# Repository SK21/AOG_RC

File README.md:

RateController (RC) is an add-on app that works with AgOpenGPS (https://github.com/agopengps-official/AgOpenGPS/) for product application rate control.

**RC Installation**
1.	Go to the latest release.
2.	Download RateControllerApp.zip
3.	Extract the file to a folder of your choice.
4.	Find and run RateController.exe

RC starts with the main screen. If AOG is connected the AOG icon will be green. There are icons for 5 products and fans. The icons will be green if connected. A module will show blue if it is sending data but not receiving. Red if there is a rate error and clear if not connected. Press the icons to show status information about the product. A graph shows the quantity remaining in the tank. Press 'Target Rate' to switch rate settings. Press Rx to use variable rate. Press 'Quantity' to switch settings. Press 'Area' to switch settings. Press quantity amount to reset tank. Press area amount to reset area.

  If there is a rate alarm due to over or under rate application a warning button will flash. The icon of the product in error will also flash. Press the warning button to silence the alarm.

  Most pages in the app menu have help available by pressing the '?'. Troubleshooting information can be found on the menu help page by pressing the '?'.

## Rate control repositories

- AOG_RC (main application)
  https://github.com/SK21/AOG_RC

- Rate_Control (module pcbs)
  https://github.com/AgOpenGPS-Official/Rate_Control

- PCBsetup (module firmware installation)
  https://github.com/SK21/PCBsetup

**Disclaimer**

This software is for discussion and learning. It is not in any way to be used on any physical equipment and is meant for use by a simulator only.

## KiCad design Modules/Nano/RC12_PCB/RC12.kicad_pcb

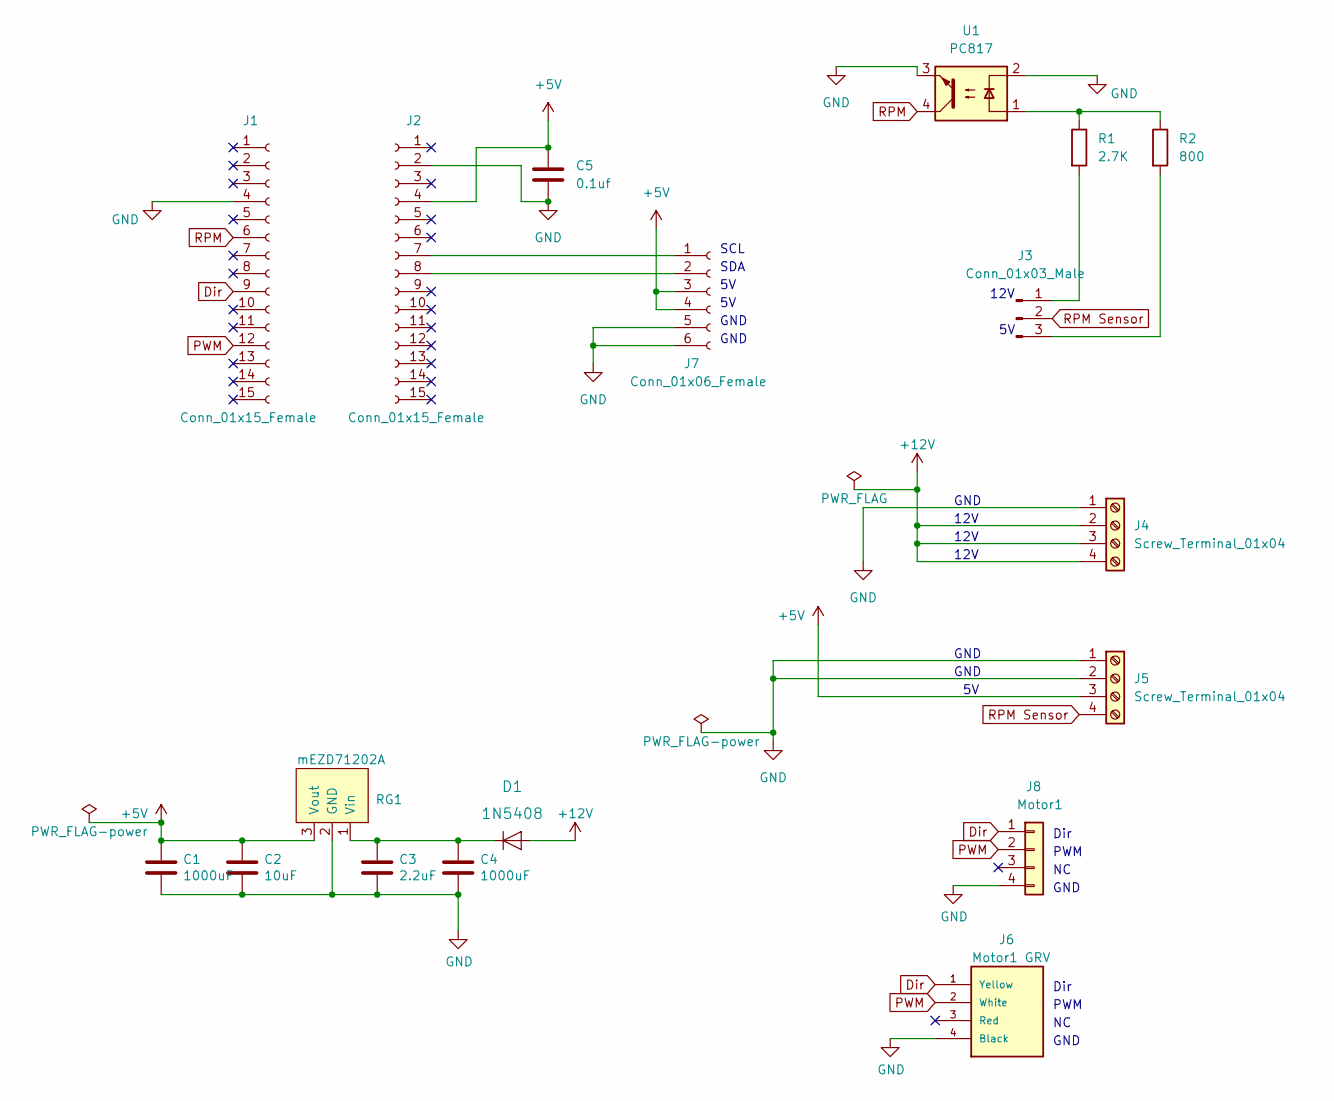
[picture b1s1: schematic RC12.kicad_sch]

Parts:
C1, C4: 1000uF; CP_Radial_D10.0mm_P5.00mm
C2: 10uF; C_Disc_D5.0mm_W2.5mm_P2.50mm
C3: 2.2uF; C_Disc_D5.0mm_W2.5mm_P2.50mm
C5: 0.1uf; C_Disc_D5.0mm_W2.5mm_P2.50mm
D1: 1N5408
J1, J2: Conn_01x15_Female; PinSocket_1x15_P2.54mm_Vertical
J3: Conn_01x03_Male; PinHeader_1x03_P2.54mm_Vertical
J4, J5: Screw_Terminal_01x04; TerminalBlock_Phoenix_PT-1,5-4-5.0-H_1x04_P5.00mm_Horizontal
J6: Motor1 GRV; Grove
J7: Conn_01x06_Female; PinSocket_1x06_P2.54mm_Vertical
J8: Motor1; Molex_KK-254_AE-6410-04A_1x04_P2.54mm_Vertical
R1: 2.7K; R_Axial_DIN0207_L6.3mm_D2.5mm_P10.16mm_Horizontal
R2: 800; R_Axial_DIN0207_L6.3mm_D2.5mm_P10.16mm_Horizontal
RG1: mEZD71202A; mEZD71201A
U1: PC817

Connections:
+5V: C1.1, C2.1, C5.2, J2.4, J5.3, J7.3, J7.4, RG1.3 (Vout)
+12V: D1.2 (A), J4.2, J4.3, J4.4
Dir: J1.9, J6.1 (Yellow), J8.1
GND: C1.2, C2.2, C3.2, C4.2, C5.1, J1.4, J2.2, J4.1, J5.1, J5.2, J6.4 (Black), J7.5, J7.6, J8.4, RG1.2 (GND), U1.2, U1.3
unnamed: C3.1, C4.1, D1.1 (C), RG1.1 (Vin)
unnamed: J2.7, J7.1
unnamed: J2.8, J7.2
unnamed: J3.1, R1.2
unnamed: J3.3, R2.2
unnamed: R1.1, R2.1, U1.1
PWM: J1.12, J6.2 (White), J8.2
RPM: J1.6, U1.4
RPM Sensor: J3.2, J5.4

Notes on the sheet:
SCL
SDA
Dir
12V
PWM
GND

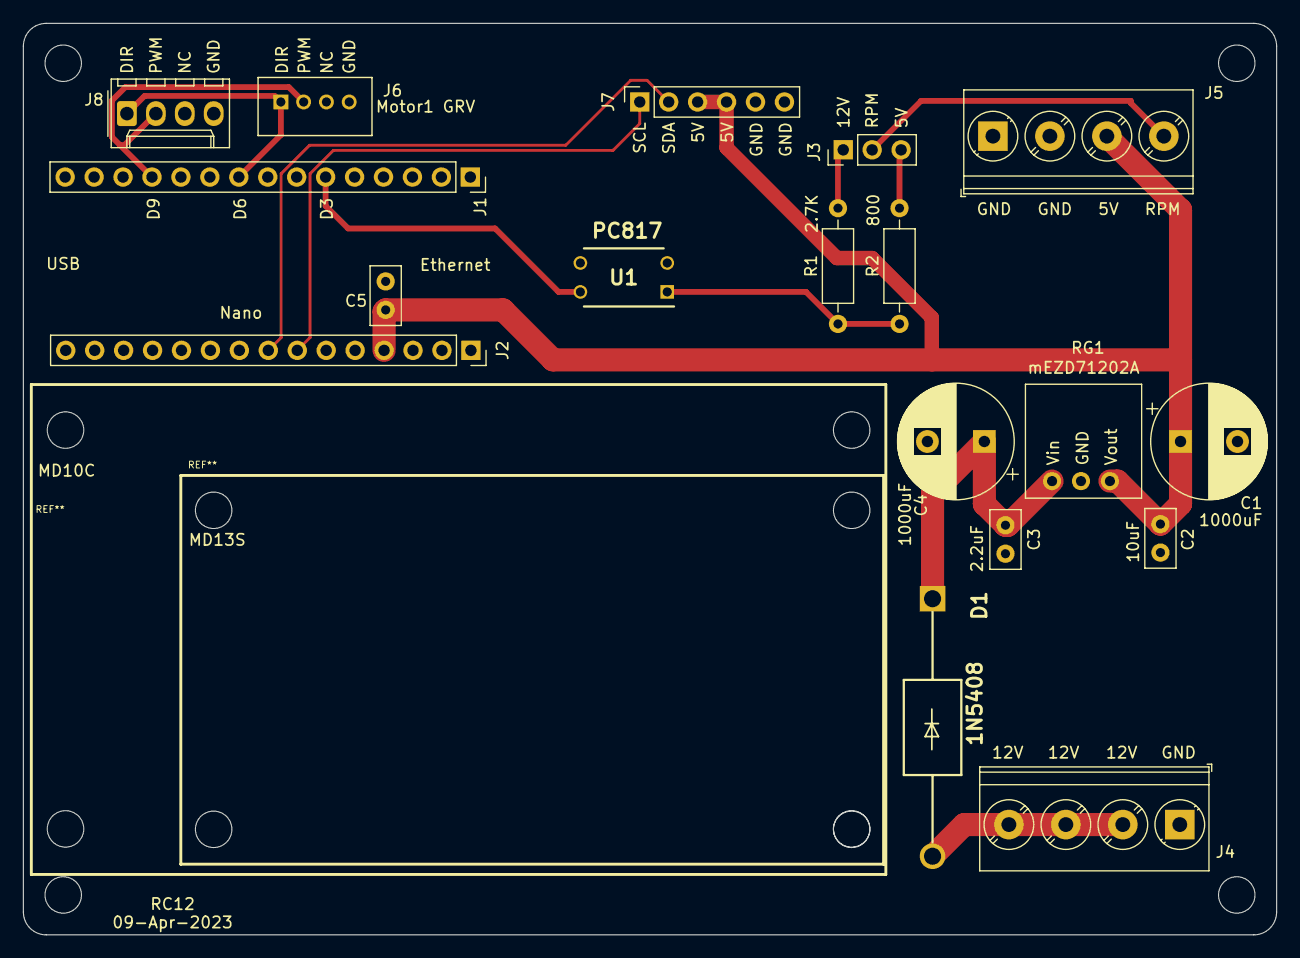
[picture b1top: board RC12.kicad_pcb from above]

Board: 2 copper layers, 110.0 x 80.0 mm, 22 parts (0 on the bottom side), 13 nets.

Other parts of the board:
 : MountingHole_3.2mm_M3
 #2,  #3,  #4: MountingHole_3.2mm_M3

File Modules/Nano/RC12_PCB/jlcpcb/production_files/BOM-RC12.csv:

Comment,Designator,Footprint,LCSC
PC817,U1,PC817,https://www.lcsc.com/product-detail/_Sharp-Microelectronics-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
,,PC817 socket,https://www.lcsc.com/product-detail/_Nextron-Nextronics-Engi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
Conn_01x15_Female,J2,PinSocket_1x15_P2.54mm_Vertical,
2.2uF,C3,C_Disc_D5.0mm_W2.5mm_P2.50mm,
Conn_01x15_Female,J1,PinSocket_1x15_P2.54mm_Vertical,
1000uF,C4,CP_Radial_D10.0mm_P5.00mm,
Screw_Terminal_01x04,J5,"TerminalBlock_Phoenix_PT-1,5-4-5.0-H_1x04_P5.00mm_Horizontal",
1000uF,C1,CP_Radial_D10.0mm_P5.00mm,
10uF,C2,C_Disc_D5.0mm_W2.5mm_P2.50mm,
Motor1 GRV,J6,Grove,https://jlcpcb.com/partdetail/SeeedStudio-110990030/C403774
0.1uf,C5,C_Disc_D5.0mm_W2.5mm_P2.50mm,
Screw_Terminal_01x04,J4,"TerminalBlock_Phoenix_PT-1,5-4-5.0-H_1x04_P5.00mm_Horizontal",
2.7K,R1,R_Axial_DIN0207_L6.3mm_D2.5mm_P10.16mm_Horizontal,
Conn_01x03_Male,J3,PinHeader_1x03_P2.54mm_Vertical,
800,R2,R_Axial_DIN0207_L6.3mm_D2.5mm_P10.16mm_Horizontal,
1N5408,D1,1N5408,
mEZD71202A,RG1,mEZD71201A,
Motor1,J8,Molex_KK-254_AE-6410-04A_1x04_P2.54mm_Vertical,https://www.lcsc.com/product-detail/_TE-Connectivity-_C86504.html
Conn_01x06_Female,J7,PinSocket_1x06_P2.54mm_Vertical,

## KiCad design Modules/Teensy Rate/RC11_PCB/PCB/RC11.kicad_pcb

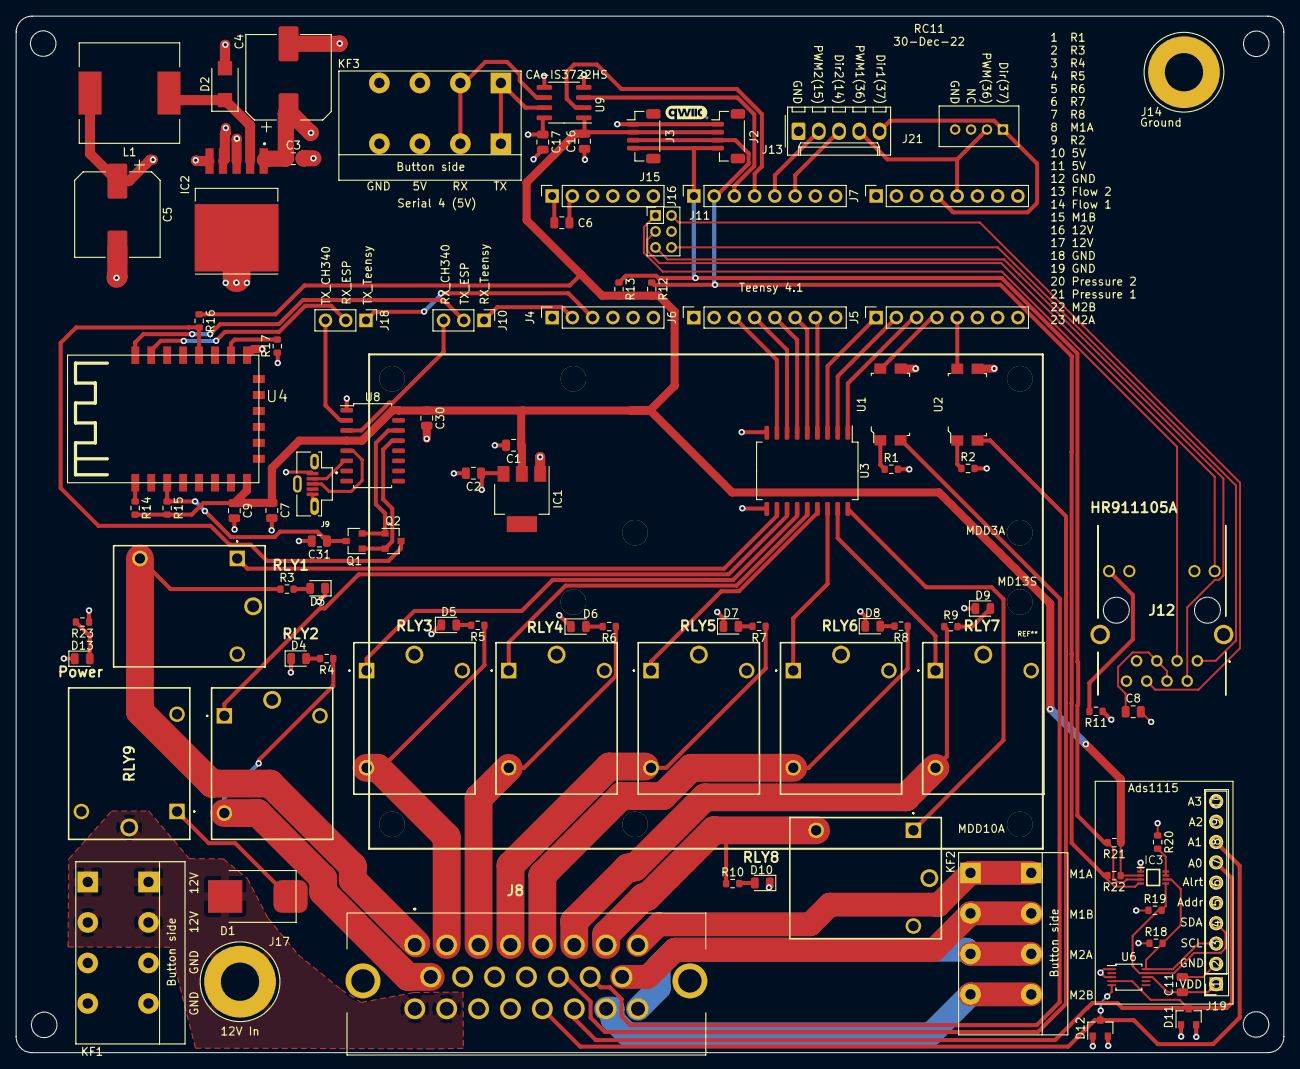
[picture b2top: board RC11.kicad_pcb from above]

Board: 4 copper layers, 159.0 x 130.0 mm, 98 parts (0 on the bottom side), 86 nets.

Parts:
 : MountingHole_3.2mm_M3
 #2,  #3,  #4: MountingHole_3.2mm_M3
C1: 22uF; C_0805_2012Metric
C2, C7: 10uF; C_0805_2012Metric
C3, C31: 1uF; C_0805_2012Metric
C4: 470uF; CP_Elec_10x10.5
C5: 330uF; CP_Elec_10x10.5
C6, C8, C9, C11, C16, C17, C30: 0.1uF; C_0805_2012Metric
D1: S10MC; D_SMC_larger_pads
D2: SS36; SMA(DO-214AC)
D3, D4, D5, D6, D7, D8, D9, D10, D13: LED; LED_0805_2012Metric
D11, D12: BAV99; SOT-23
IC1: AZ1117; SOT-223
IC2: XL2596; TO263-5L
IC3: PCA9306DCUR
J2, J3: I2C-3V3; Qwic_vertical
J4, J15: Conn_01x06_Female; PinSocket_1x06_P2.54mm_Vertical
J5, J6, J7, J16: Conn_01x08_Female; PinSocket_1x08_P2.54mm_Vertical
J8: 776087-1; 7760871
J9: 105133-0011; MOLEX_105133-0011
J10, J18: Conn_01x03_Male; PinHeader_1x03_P2.54mm_Vertical
J11: Teensy_Ethernet; PinHeader_2x03_P2.00mm_Vertical
J12: HR911105A
J13: Conn_01x05; Molex_KK-254_AE-6410-05A_1x05_P2.54mm_Vertical
J14: Ground; PowerPin
J17: 12V In; PowerPin
J19: ADS1115 - 1001001; PinSocket_1x10_P2.54mm_Vertical
J21: Motor1 GRV; Grove
KF1, KF2: KF142V-5.0-4P; KF142V-5.08-4P
KF3: Serial 4 (5V); KF142V-5.08-4P
L1: SMDRI127-330MT; TMPA1265SP-101MN-D
Q1, Q2: BSS138; SOT-23
R1, R2: 200; R_0603_1608Metric
R3, R4, R5, R6, R7, R8, R9, R10, R23: 500; R_0603_1608Metric
R11: 150; R_0603_1608Metric
R12, R13: 2.2K; R_0603_1608Metric
R14, R15, R16, R17: 10K; R_0603_1608Metric
R18, R19: 341; R_0603_1608Metric
R20: 200K; R_0603_1608Metric
R21, R22: 217; R_0603_1608Metric
RLY1, RLY2, RLY3, RLY4, RLY5, RLY6, RLY7, RLY8, RLY9: HF3FF_012-1HST_257_; HF3FF0121HST257
U1, U2: PC817; SMD-4_4.6x7.62mm_P2.54mm
U3: ULN2803A; SOP-18_7x12.5mm_P1.27mm
U4: ESP-12F
U6: ADS1115IDGS - 1001000; TSSOP-10_3x3mm_P0.5mm
U8: CH340C; SOP-16_4.55x10.3mm_P1.27mm
U9: CA-IS3722HS; SOIC-8_3.9x4.9mm_P1.27mm

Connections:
12V_In: D1.2, J8.16, J8.17, J17.1, KF1.1, KF1.2, RLY9.2
+3V3: C1.1, C7.1, C9.1, C16.2, C30.1, IC1.2, IC3.2, J2.2, J3.2, R12.2, R13.2, R14.2, R15.2, R16.1, R21.1, R22.1, U4.8, U8.4, U8.16, U9.1
+5V: C2.1, C5.1, C6.1, C11.1, C17.1, D11.2, D12.2, IC1.3, IC2.4, J8.10, J8.11, J9.1, J15.1, J19.1, J19.5, KF3.3, L1.2, R1.2, R2.2, R11.1, R18.1, R19.1, R20.1, U6.8, U9.8
+12V: C3.1, C4.1, IC2.1, R23.1, RLY1.2, RLY1.3, RLY2.2, RLY2.3, RLY3.2, RLY3.3, RLY4.2, RLY4.3, RLY5.2, RLY5.3, RLY6.2, RLY6.3, RLY7.2, RLY7.3, RLY8.2, RLY8.3, RLY9.4, U3.10
AIN0: D11.3, J8.21, J19.7, U6.4
AIN1: D12.3, J8.20, J19.8, U6.5
EN: C31.1, Q1.3, R15.1, U4.3
FlowPin1: J5.4, U1.4
FlowPin2: J5.5, U2.4
GND: C1.2, C2.2, C3.2, C4.2, C5.2, C6.2, C7.2, C8.2, C9.2, C11.2, C16.1, C17.2, C30.2, C31.2, D2.2, D3.1, D4.1, D5.1, D6.1, D7.1, D8.1, D9.1, D10.1, D11.1, D12.1, D13.1, IC1.1, IC2.3, IC2.5, IC2.6, IC3.1, J2.1, J3.1, J4.1, J8.12, J8.18, J8.19, J9.5, J9.S1, J9.S2, J9.S3, J11.4, J12.8, J12.10, J12.11, J12.MH1, J12.MH2, J13.1, J14.1, J15.2, J16.8, J19.2, J21.4, KF1.3, KF1.4, KF3.4, R17.1, RLY9.3, U1.3, U2.3, U3.9, U4.15, U6.1, U6.3, U8.1, U9.4, U9.5
IO0: Q2.3, R16.2, U4.18
IO14: J13.3, J16.6
IO15: J13.2, J16.5
IO36: J7.5, J13.4, J21.2
IO37: J7.4, J13.5, J21.1
unnamed: C8.1, J12.4, J12.5
unnamed: D1.1, RLY9.1
unnamed: D2.1, IC2.2, L1.1
unnamed: D3.2, R3.2
unnamed: D4.2, R4.2
unnamed: D5.2, R5.2
unnamed: D6.2, R6.2
unnamed: D7.2, R7.2
unnamed: D8.2, R8.2
unnamed: D9.2, R9.2
unnamed: D10.2, R10.2
unnamed: D13.2, R23.2
unnamed: IC3.5, J19.4, R19.2, U6.9
unnamed: IC3.6, J19.3, R18.2, U6.10
unnamed: IC3.7, IC3.8, R20.2
unnamed: J8.8, KF2.1
unnamed: J8.15, KF2.2
unnamed: J8.22, KF2.4
unnamed: J8.23, KF2.3
unnamed: J9.2, U8.6
unnamed: J9.3, U8.5
unnamed: J11.1, J12.3
unnamed: J11.2, J12.6
unnamed: J11.3, J12.9
unnamed: J11.5, J12.2
unnamed: J11.6, J12.1
unnamed: J12.12, R11.2
unnamed: KF3.1, U9.7
unnamed: KF3.2, U9.6
unnamed: Q1.1, Q2.2, U8.13
unnamed: Q1.2, Q2.1, U8.14
unnamed: R1.1, U1.1
unnamed: R2.1, U2.1
unnamed: R14.1, U4.1
unnamed: R17.2, U4.16
unnamed: RLY1.1, U3.11
unnamed: RLY2.1, U3.12
unnamed: RLY3.1, U3.13
unnamed: RLY4.1, U3.14
unnamed: RLY5.1, U3.15
unnamed: RLY6.1, U3.16
unnamed: RLY7.1, U3.17
unnamed: RLY8.1, U3.18
R1: J8.1, R3.1, RLY1.4
R2: J8.9, R4.1, RLY2.4
R3: J8.2, R5.1, RLY3.4
R4: J8.3, R6.1, RLY4.4
R5: J8.4, R7.1, RLY5.4
R6: J8.5, R8.1, RLY6.4
R7: J8.6, R9.1, RLY7.4
R8: J8.7, R10.1, RLY8.4
RLY1: J6.3, U3.8
RLY2: J6.4, U3.7
RLY3: J6.5, U3.6
RLY4: J6.6, U3.5
RLY5: J6.7, U3.4
RLY6: J5.1, U3.3
RLY7: J5.2, U3.2
RLY8: J5.3, U3.1
RX4: J16.4, U9.2
RX_CH340: J10.3, U8.3
RX_ESP: J18.2, U4.21
RX_Teensy: J4.2, J10.1
SCL_Teensy: IC3.3, J2.4, J3.4, J16.1, R13.1, R21.2
SDA_Teensy: IC3.4, J2.3, J3.3, J16.2, R12.1, R22.2
Sensor1: J8.14, U1.2
Sensor2: J8.13, U2.2
TX4: J16.3, U9.3
TX_CH340: J18.3, U8.2
TX_ESP: J10.2, U4.22
TX_Teensy: J4.3, J18.1

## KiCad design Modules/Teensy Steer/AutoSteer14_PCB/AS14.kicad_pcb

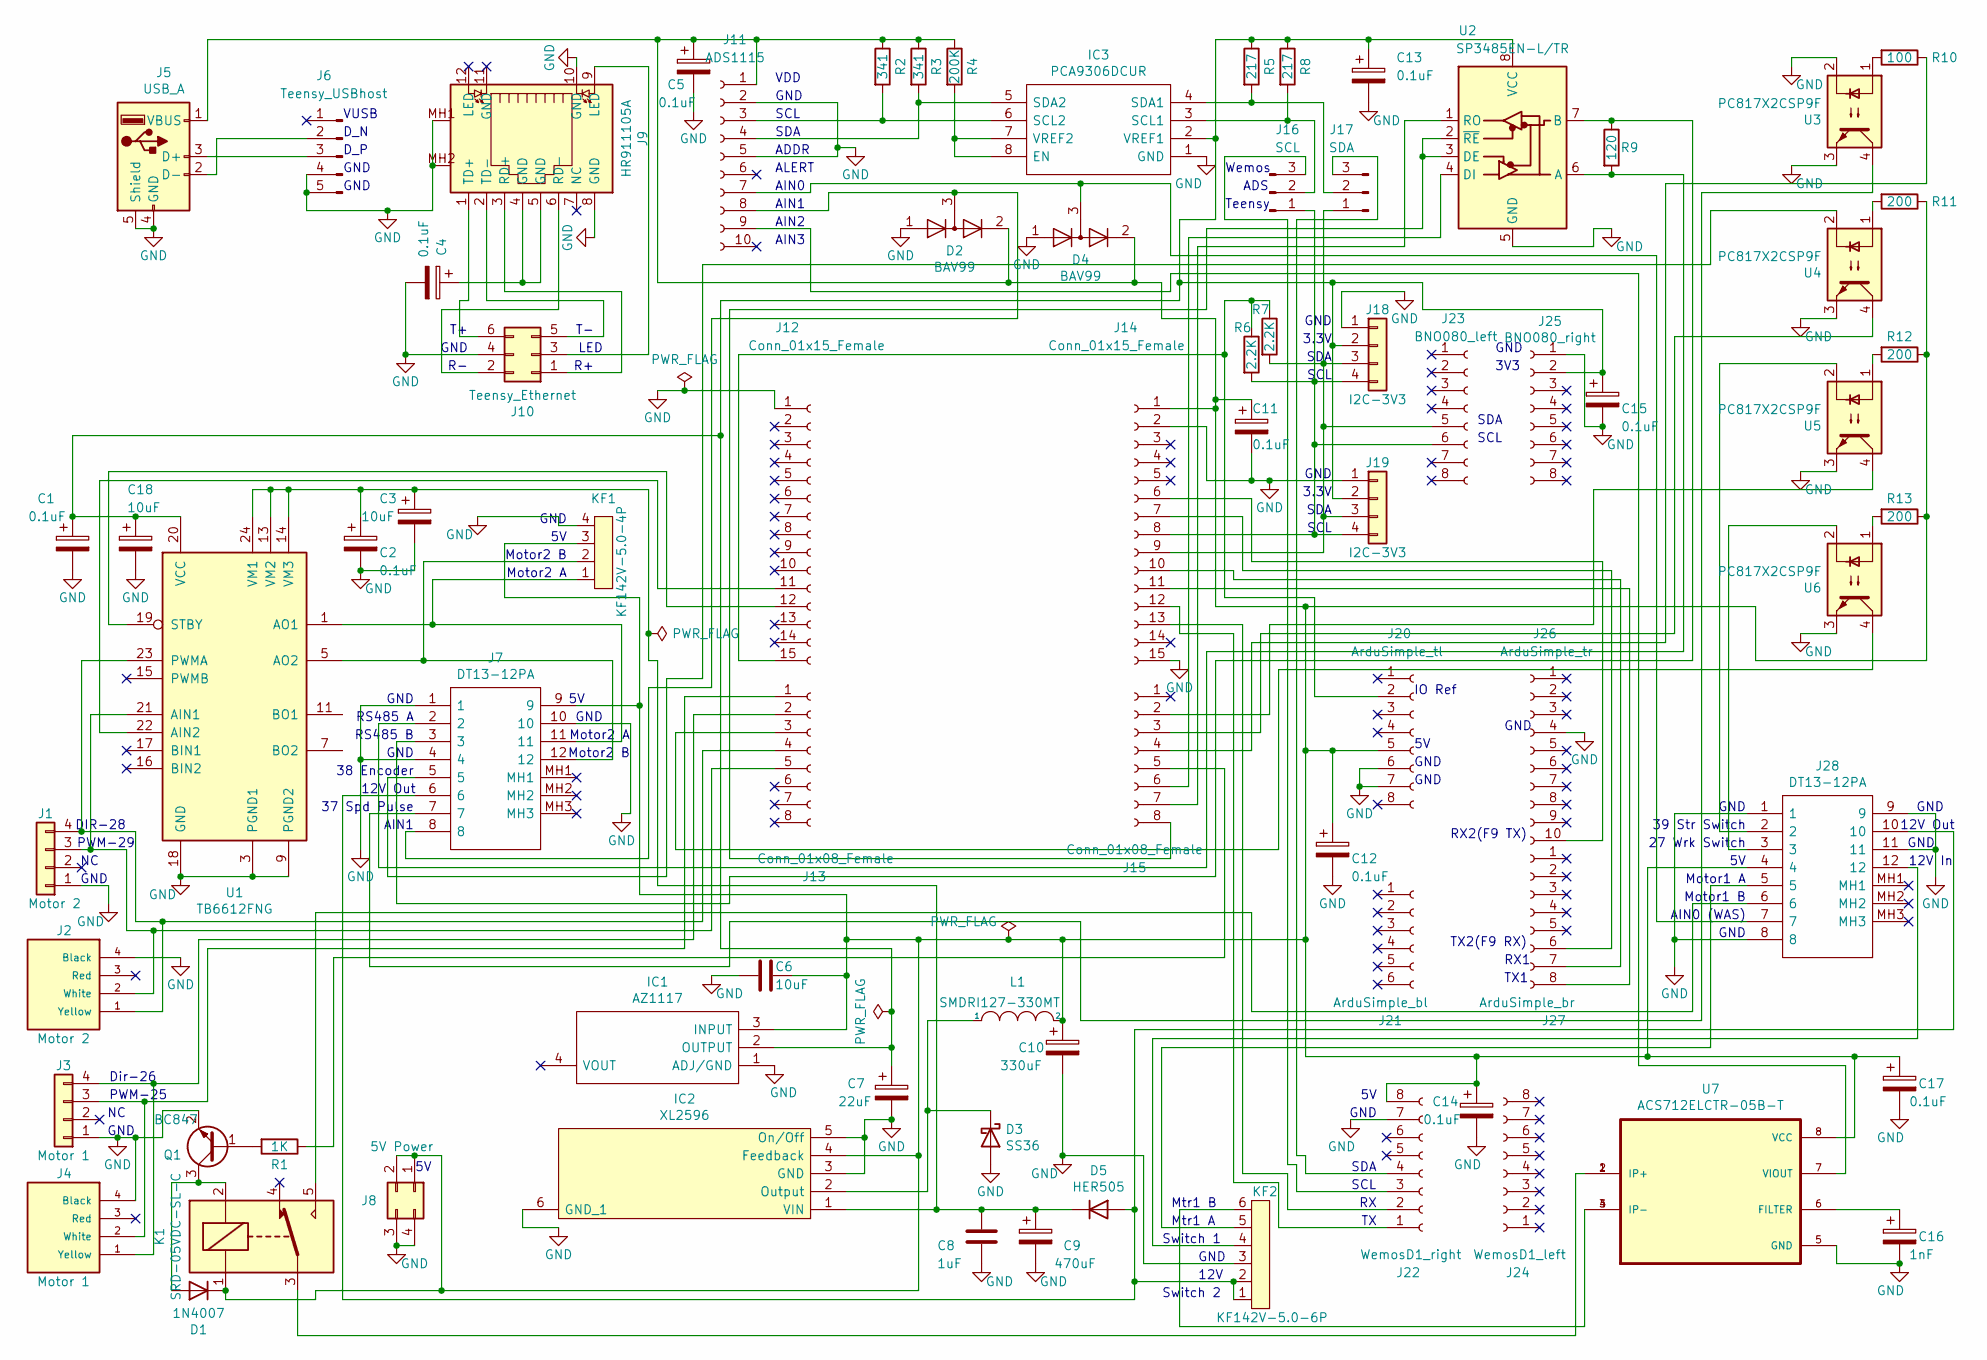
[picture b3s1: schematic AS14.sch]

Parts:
C1, C2, C4, C5, C11, C12, C13, C14, C15, C17: 0.1uF; C_0805_2012Metric
C3, C6, C18: 10uF; C_0805_2012Metric
C7: 22uF; C_0805_2012Metric
C8: 1uF; C_0805_2012Metric
C9: 470uF; CP_Elec_10x10.5
C10: 330uF; CP_Elec_10x10.5
C16: 1nF; C_0805_2012Metric
D1: 1N4007; D_SMA
D2, D4: BAV99; SOT-23
D3: SS36; SMA(DO-214AC)
D5: HER505; 1N5408
IC1: AZ1117; SOT-223
IC2: XL2596; TO263-5L
IC3: PCA9306DCUR; Mouser Part Number 595-PCA9306DCUR
J1: Motor 2; Qwic_vertical
J2: Motor 2; Grove
J3: Motor 1; Qwic_vertical
J4: Motor 1; Grove
J5: USB_A; USB_A_Molex_67643_Horizontal
J6: Teensy_USBhost; PinHeader_1x05_P2.54mm_Vertical
J7, J28: DT13-12PA; DT1312PA; Manufacturer_Part_Number DT13-12PA; Mouser Part Number 571-DT13-12PA
J8: 5V Power; PinSocket_2x02_P2.54mm_Vertical
J9: HR911105A
J10: Teensy_Ethernet; PinHeader_2x03_P2.00mm_Vertical
J11: ADS1115; PinSocket_1x10_P2.54mm_Vertical
J12, J14: Conn_01x15_Female; PinSocket_1x15_P2.54mm_Vertical
J13, J15: Conn_01x08_Female; PinSocket_1x08_P2.54mm_Vertical
J16: SCL; PinHeader_1x03_P2.54mm_Vertical
J17: SDA; PinHeader_1x03_P2.54mm_Vertical
J18, J19: I2C-3V3; Qwic_vertical
J20: ArduSimple_tl; PinSocket_1x08_P2.54mm_Vertical
J21: ArduSimple_bl; PinSocket_1x06_P2.54mm_Vertical
J22: WemosD1_right; PinSocket_1x08_P2.54mm_Vertical
J23: BNO080_left; PinSocket_1x08_P2.54mm_Vertical
J24: WemosD1_left; PinSocket_1x08_P2.54mm_Vertical
J25: BNO080_right; PinSocket_1x08_P2.54mm_Vertical
J26: ArduSimple_tr; PinSocket_1x10_P2.54mm_Vertical
J27: ArduSimple_br; PinSocket_1x08_P2.54mm_Vertical
K1: SRD-05VDC-SL-C; Songle_SRD-05VDC-SL-C
KF1: KF142V-5.0-4P; KF142V-5.08-4P
KF2: KF142V-5.0-6P; KF142V-5.08-6P
L1: SMDRI127-330MT; TMPA1265SP-101MN-D
Q1: BC847; SOT-23
R1: 1K; R_1206_3216Metric
R2, R3: 341; R_1206_3216Metric
R4: 200K; R_1206_3216Metric
R5, R8: 217; R_1206_3216Metric
R6, R7: 2.2K; R_1206_3216Metric
R9: 120; R_1206_3216Metric
R10: 100; R_1206_3216Metric
R11, R12, R13: 200; R_1206_3216Metric
U1: TB6612FNG; SSOP-24_5.3x8.2mm_P0.65mm
U2: SP3485EN-L/TR; Maxim_Integrated-S8-2-0-P-MFG
U3, U4, U5, U6: PC817X2CSP9F; SOIC254P960X420-4N
U7: ACS712ELCTR-05B-T; SOIC127P600X175-8N; PARTREV 1.0

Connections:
GND: C1.2, C2.2, C3.2, C4.2, C5.2, C6.2, C7.2, C8.2, C9.2, C10.2, C11.2, C12.2, C13.2, C14.2, C15.2, C16.2, C17.2, C18.2, D2.1 (K), D3.2 (A), D4.1 (K), IC1.1 (ADJ/GND), IC2.3 (GND), IC2.5 (On/Off), IC2.6 (GND_1), IC3.1 (GND), J1.1, J2.4 (Black), J3.1, J4.4 (Black), J5.4 (GND), J5.5 (Shield), J6.4, J6.5, J7.1, J7.4, J7.10, J8.3, J8.4, J9.8 (GND), J9.10 (GND), J9.MH1, J9.MH2, J10.4, J11.2, J11.5, J12.1, J14.2, J14.15, J18.1, J19.1, J20.6, J20.7, J22.7, J25.1, J26.4, J28.1, J28.8, J28.9, J28.11, KF1.4, KF2.3, Q1.2 (E), U1.3 (PGND1), U1.4 (PGND1), U1.9 (PGND2), U1.10 (PGND2), U1.18 (GND), U2.5 (GND), U3.2, U3.3, U4.3, U5.3, U6.3, U7.5 (GND)
unnamed: C1.1, C7.1, C13.1, C15.1, C18.1, IC1.2 (OUTPUT), IC3.2 (VREF1), J18.2, J19.2, J25.2, R5.1, R8.1, U1.20 (VCC), U2.8 (VCC)
unnamed: C2.1, C3.1, C8.1, C9.1, D5.1 (K), IC2.1 (VIN), U1.13 (VM2), U1.14 (VM3), U1.24 (VM1)
unnamed: C4.1, J9.4 (GND), J9.5 (GND)
unnamed: C5.1, C6.1, C10.1, C11.1, C12.1, C14.1, C17.1, D1.1 (K), D2.2 (A), D4.2 (A), IC1.3 (INPUT), IC2.4 (Feedback), J5.1 (VBUS), J7.9, J8.1, J8.2, J11.1, J14.1, J20.5, J22.8, J28.4, K1.1, KF1.3, L1.2, R2.1, R3.1, R4.1, R11.1, R12.1, R13.1, U7.8 (VCC)
unnamed: C16.1, U7.6 (FILTER)
unnamed: D1.2 (A), K1.2, Q1.3 (C)
unnamed: D2.3 (K), J7.8, J11.8
unnamed: D3.1 (K), IC2.2 (Output), L1.1
unnamed: D4.3 (K), J11.7, J28.7
unnamed: D5.2 (A), J7.6, J28.10, KF2.1, KF2.2
unnamed: IC3.3 (SCL1), J16.2, R8.2
unnamed: IC3.4 (SDA1), J17.2, R5.2
unnamed: IC3.5 (SDA2), J11.4, R3.2
unnamed: IC3.6 (SCL2), J11.3, R2.2
unnamed: IC3.7 (VREF2), IC3.8 (EN), R4.2
unnamed: J1.3, J2.2 (White), J13.5, U1.21 (AIN1)
unnamed: J1.4, J2.1 (Yellow), J13.4, U1.23 (PWMA)
unnamed: J5.2 (D-), J6.2
unnamed: J5.3 (D+), J6.3
unnamed: J7.2, R9.2, U2.6 (A)
unnamed: J7.3, R9.1, U2.7 (B)
unnamed: J7.5, U4.2
unnamed: J7.7, U3.4
unnamed: J7.11, KF1.1, U1.1 (AO1), U1.2 (AO1)
unnamed: J7.12, KF1.2, U1.5 (AO2), U1.6 (AO2)
unnamed: J9.3 (RD+), J10.1
unnamed: J9.6 (RD-), J10.2
unnamed: J9.9 (LED), J10.3
unnamed: J9.2 (TD-), J10.5
unnamed: J9.1 (TD+), J10.6
unnamed: J11.9, U7.7 (VIOUT)
unnamed: J12.11, U1.22 (AIN2)
unnamed: J12.12, U1.19 (STBY)
unnamed: J12.15, J20.2, R6.1, R7.1
unnamed: J3.3, J4.2 (White), J13.1
unnamed: J3.4, J4.1 (Yellow), J13.2
unnamed: J13.3, U6.4
unnamed: J14.6, J26.10
unnamed: J14.7, J27.6
unnamed: J14.8, J16.1, J18.4, J19.4, J23.6, R6.2
unnamed: J14.9, J17.1, J18.3, J19.3, J23.5, R7.2
unnamed: J14.10, J27.7
unnamed: J14.11, J27.8
unnamed: J14.12, J22.1
unnamed: J14.13, J22.2
unnamed: J15.2, U5.4
unnamed: J15.3, U4.4
unnamed: J15.4, R10.1
unnamed: J15.5, R1.1
unnamed: J15.6, U2.4 (DI)
unnamed: J15.7, U2.1 (RO)
unnamed: J15.8, U2.2 (~RE), U2.3 (DE)
unnamed: J16.3, J22.3
unnamed: J17.3, J22.4
unnamed: J28.2, U5.2
unnamed: J28.3, U6.2
unnamed: J28.5, KF2.5
unnamed: J28.6, K1.5
unnamed: J28.12, KF2.4
unnamed: K1.3, U7.1 (IP+), U7.2 (IP+)
unnamed: KF2.6, U7.3 (IP-), U7.4 (IP-)
unnamed: Q1.1 (B), R1.2
unnamed: R10.2, U3.1
unnamed: R11.2, U4.1
unnamed: R12.2, U5.1
unnamed: R13.2, U6.1
unnamed: U1.7 (BO2), U1.8 (BO2)
unnamed: U1.11 (BO1), U1.12 (BO1)

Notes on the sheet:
Dir-26
PWM-25
Mtr1 B
Switch 1
Mtr1 A
SCL
SDA
3.3V
GND
IO Ref
RX2(F9 TX)
Switch 2
12V
PWM-29
DIR-28
Motor2 B
3V3
Motor2 A
12V Out
TX2(F9 RX)
RX1
TX1
LED
VDD
ADDR
ALERT
AIN0
AIN1
AIN2
AIN3
12V In
ADS
Teensy
Wemos
Motor1 A
Motor1 B
27 Wrk Switch
37 Spd Pulse
39 Str Switch
RS485 A

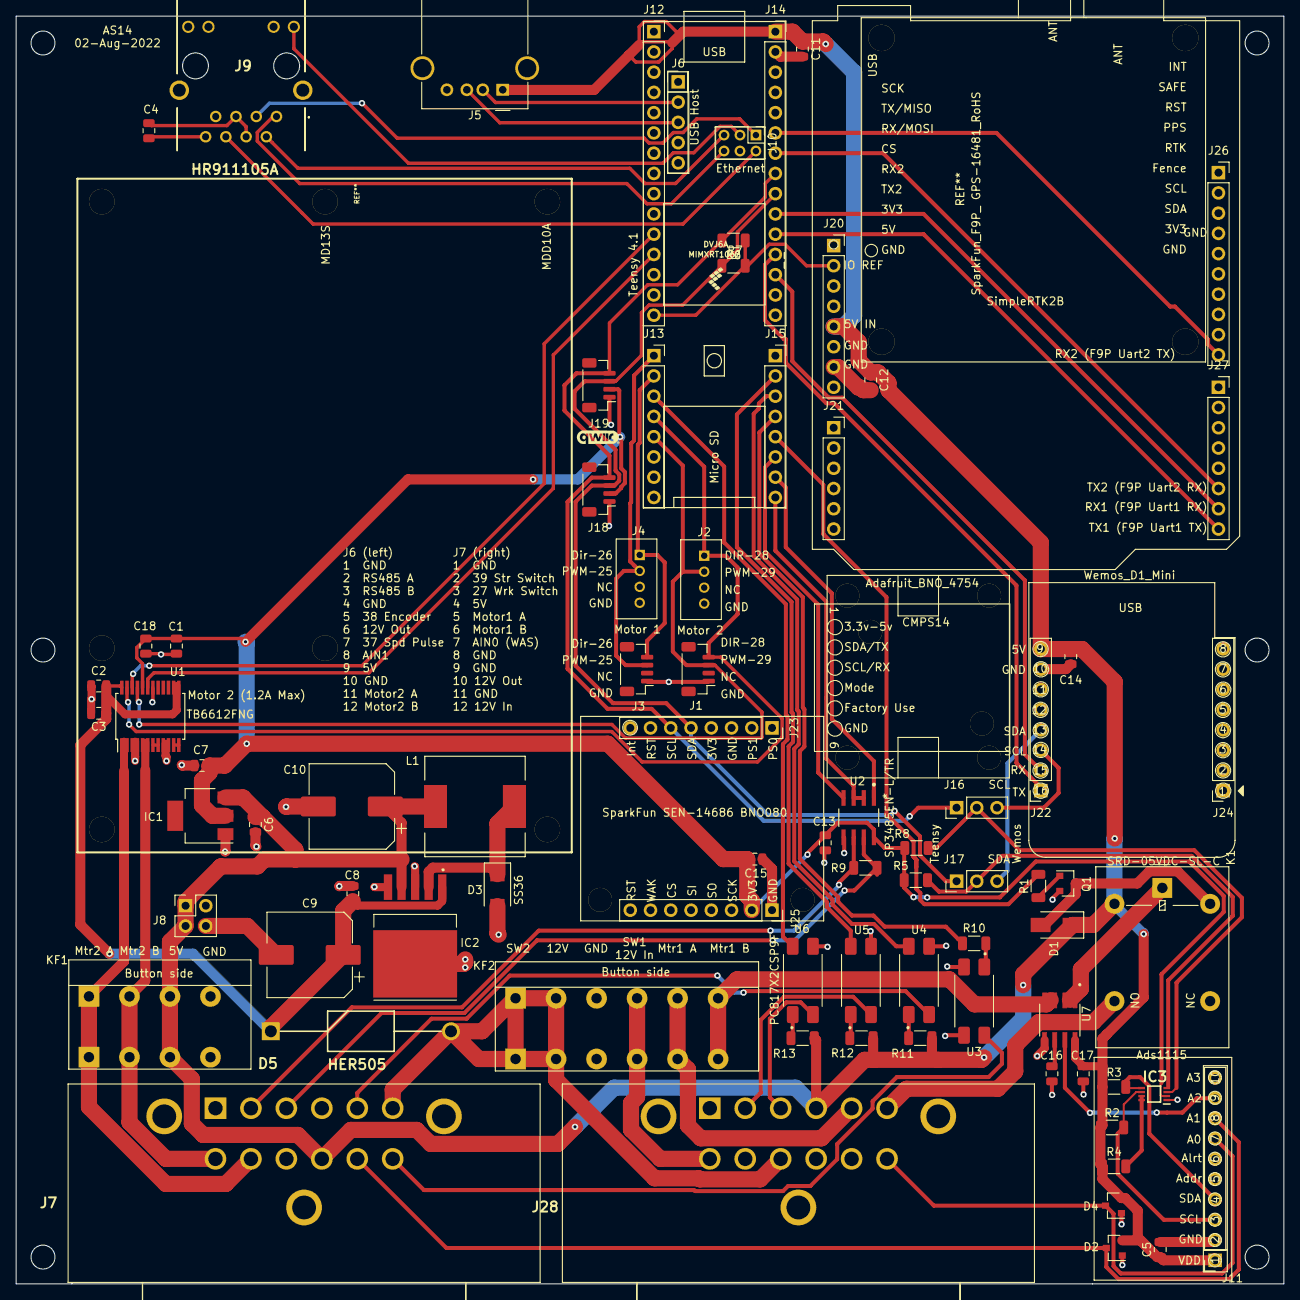
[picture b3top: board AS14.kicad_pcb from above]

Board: 2 copper layers, 159.0 x 159.0 mm, 87 parts (0 on the bottom side), 69 nets.

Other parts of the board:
 : MountingHole_3mm
 #2,  #3,  #4,  #5,  #6: MountingHole_3mm
--: Teensy 4.1; Teensy41_no_pins
M1: CMPS14; CMPS14_no_pins

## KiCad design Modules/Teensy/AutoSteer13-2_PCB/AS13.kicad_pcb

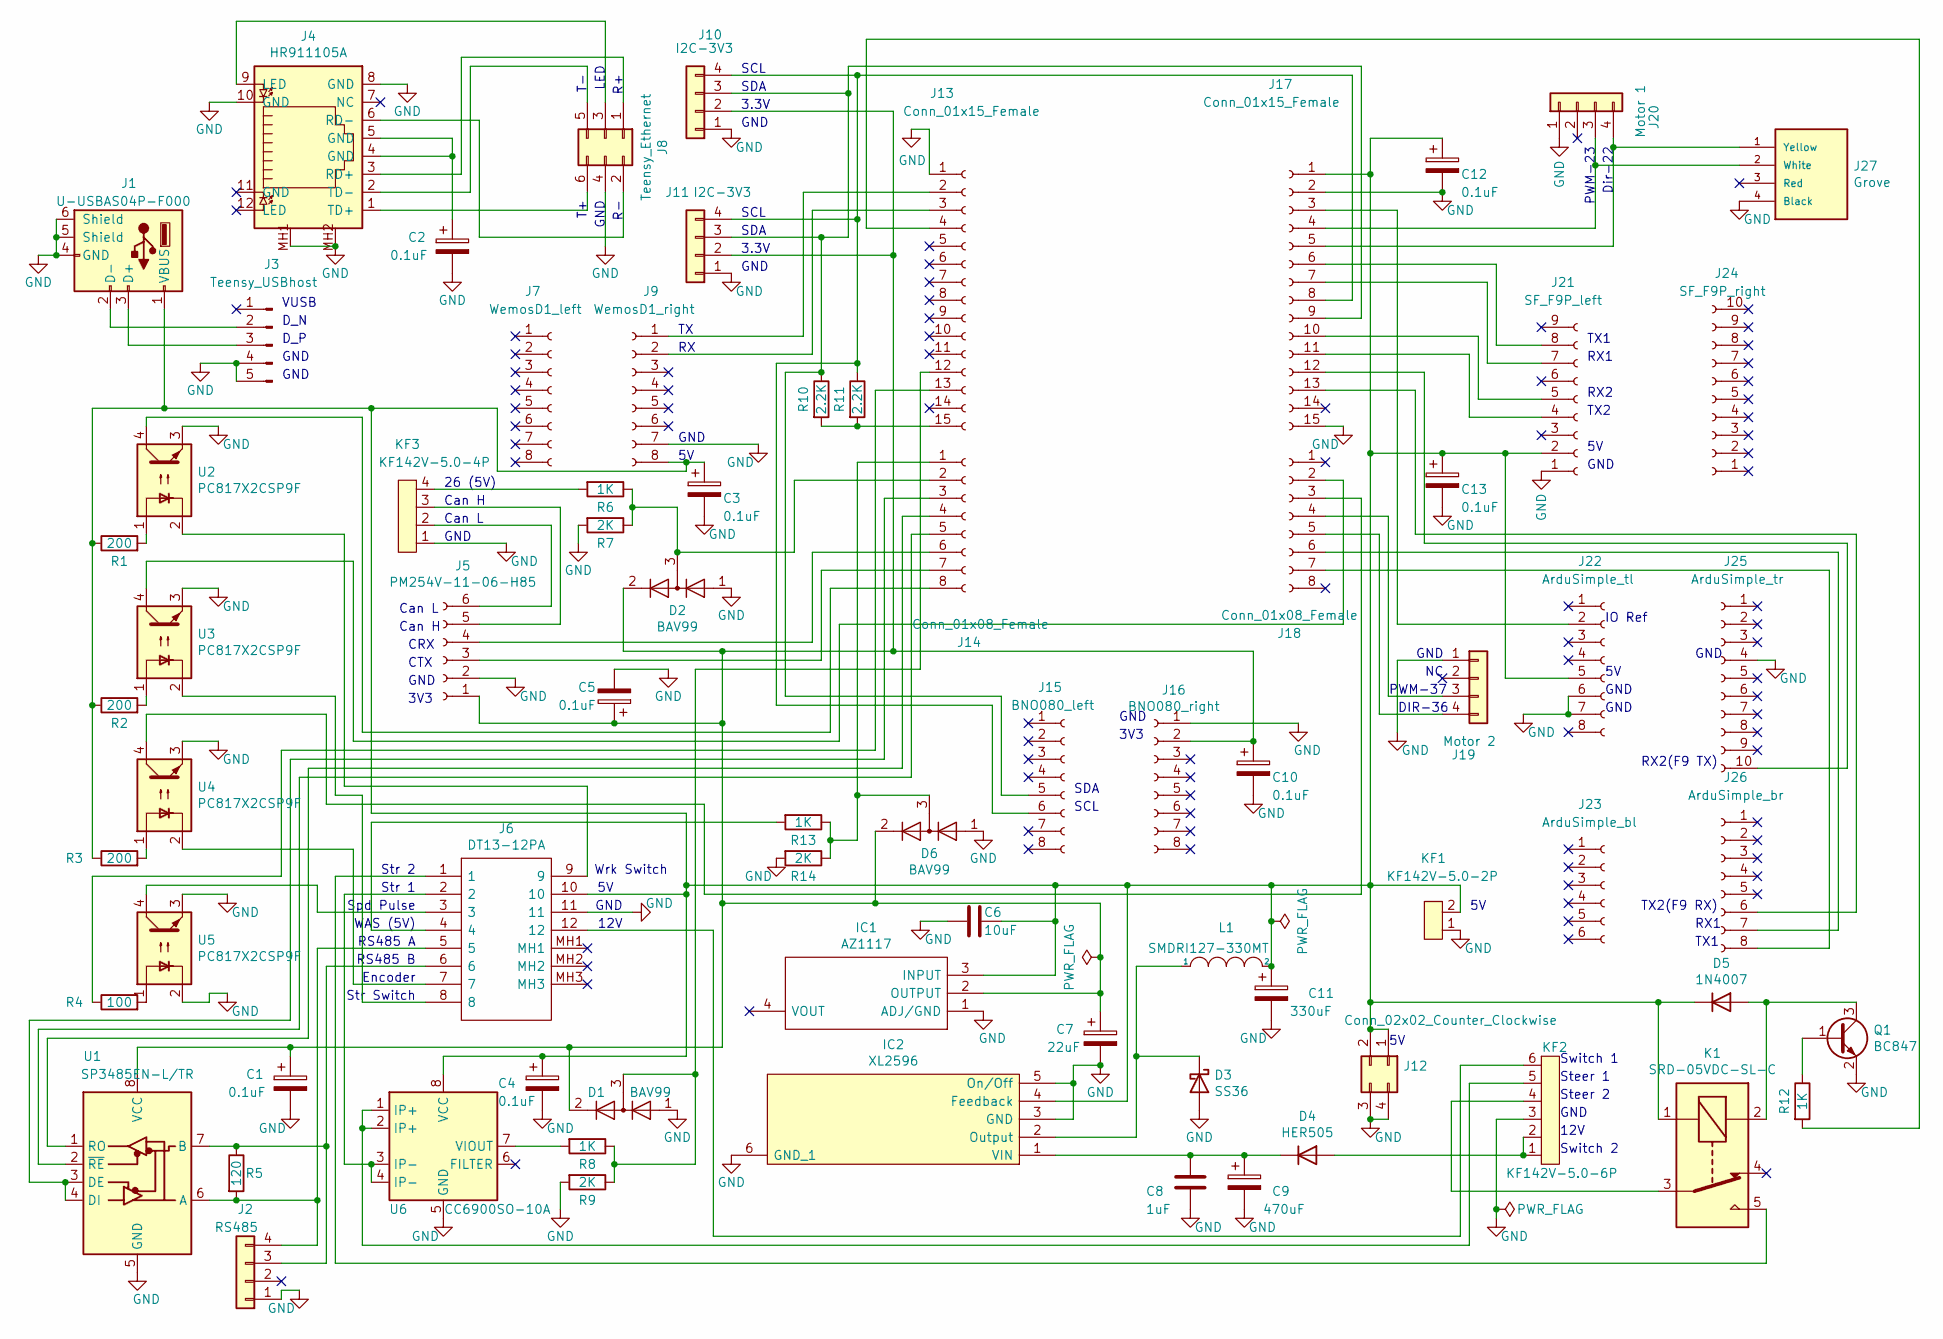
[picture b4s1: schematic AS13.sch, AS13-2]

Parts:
C1, C2, C3, C4, C5, C10, C12, C13: 0.1uF; C_0805_2012Metric
C6: 10uF; C_0805_2012Metric
C7: 22uF; C_0805_2012Metric
C8: 1uF; C_0805_2012Metric
C9: 470uF; CP_Elec_10x10.5
C11: 330uF; CP_Elec_10x10.5
D1, D2, D6: BAV99; SOT-23
D3: SS36; SMA(DO-214AC)
D4: HER505; 1N5408
D5: 1N4007; D_SMA
IC1: AZ1117; SOT-223
IC2: XL2596; TO263-5L
J1: U-USBAS04P-F000
J2: RS485; Qwic_vertical
J3: Teensy_USBhost; PinHeader_1x05_P2.54mm_Vertical
J4: HR911105A
J5: PM254V-11-06-H85; PinSocket_1x06_P2.54mm_Vertical
J6: DT13-12PA; DT1312PA; Manufacturer_Part_Number DT13-12PA; Mouser Part Number 571-DT13-12PA
J7: WemosD1_left; PinSocket_1x08_P2.54mm_Vertical
J8: Teensy_Ethernet; PinHeader_2x03_P2.00mm_Vertical
J9: WemosD1_right; PinSocket_1x08_P2.54mm_Vertical
J10, J11: I2C-3V3; Qwic_vertical
J12: Conn_02x02_Counter_Clockwise; PinSocket_2x02_P2.54mm_Vertical
J13, J17: Conn_01x15_Female; PinSocket_1x15_P2.54mm_Vertical
J14, J18: Conn_01x08_Female; PinSocket_1x08_P2.54mm_Vertical
J15: BNO080_left; PinSocket_1x08_P2.54mm_Vertical
J16: BNO080_right; PinSocket_1x08_P2.54mm_Vertical
J19: Motor 2; Qwic_vertical
J20: Motor 1; Qwic_vertical
J21: SF_F9P_left; PinSocket_1x09_P2.54mm_Vertical
J22: ArduSimple_tl; PinSocket_1x08_P2.54mm_Vertical
J23: ArduSimple_bl; PinSocket_1x06_P2.54mm_Vertical
J24: SF_F9P_right; PinSocket_1x10_P2.54mm_Vertical
J25: ArduSimple_tr; PinSocket_1x10_P2.54mm_Vertical
J26: ArduSimple_br; PinSocket_1x08_P2.54mm_Vertical
J27: Grove
K1: SRD-05VDC-SL-C; Songle_SRD-05VDC-SL-C
KF1: KF142V-5.0-2P; KF142V-5.08-2P
KF2: KF142V-5.0-6P; KF142V-5.08-6P
KF3: KF142V-5.0-4P; KF142V-5.08-4P
L1: SMDRI127-330MT; TMPA1265SP-101MN-D
Q1: BC847; SOT-23
R1, R2, R3: 200; R_1206_3216Metric
R4: 100; R_1206_3216Metric
R5: 120; R_1206_3216Metric
R6, R8, R12, R13: 1K; R_1206_3216Metric
R7, R9, R14: 2K; R_1206_3216Metric
R10, R11: 2.2K; R_1206_3216Metric
U1: SP3485EN-L/TR; Maxim_Integrated-S8-2-0-P-MFG
U2, U3, U4, U5: PC817X2CSP9F; SOIC254P960X420-4N
U6: CC6900SO-10A; SOIC127P600X175-8N

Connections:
GND: C1.2, C2.2, C3.2, C4.2, C5.2, C6.2, C7.2, C8.2, C9.2, C10.2, C11.2, C12.2, C13.2, D1.1 (K), D2.1 (K), D3.2 (A), D6.1 (K), IC1.1 (ADJ/GND), IC2.3 (GND), IC2.5 (On/Off), IC2.6 (GND_1), J1.4 (GND), J1.5 (Shield), J1.6 (Shield), J2.1, J3.4, J3.5, J4.8 (GND), J4.10 (GND), J4.MH1, J4.MH2, J5.2, J6.11, J8.4, J9.7, J10.1, J11.1, J12.3, J12.4, J13.1, J16.1, J17.2, J17.15, J19.1, J20.1, J21.1, J22.6, J22.7, J25.4, J27.4 (Black), KF1.1, KF2.3, KF3.1, Q1.2 (E), R7.2, R9.2, R14.2, U1.5 (GND), U2.3, U3.3, U4.3, U5.2, U5.3, U6.5 (GND)
unnamed: C1.1, C5.1, C7.1, C10.1, D1.2 (A), D2.2 (A), D6.2 (A), IC1.2 (OUTPUT), J5.1, J10.2, J11.2, J16.2, U1.8 (VCC)
unnamed: C2.1, J4.4 (GND), J4.5 (GND)
unnamed: C8.1, C9.1, D4.1 (K), IC2.1 (VIN)
unnamed: C3.1, C4.1, C6.1, C11.1, C12.1, C13.1, D5.1 (K), IC1.3 (INPUT), IC2.4 (Feedback), J1.1 (VBUS), J6.10, J9.8, J12.1, J12.2, J17.1, J21.2, J22.5, K1.1, KF1.2, L1.2, R1.1, R2.1, R3.1, U6.8 (VCC)
unnamed: D1.3 (K), J13.12, R8.1, R9.1
unnamed: D2.3 (K), J14.2, R6.1, R7.1
unnamed: D3.1 (K), IC2.2 (Output), L1.1
unnamed: D4.2 (A), KF2.1, KF2.2
unnamed: D5.2 (A), K1.2, Q1.3 (C)
unnamed: D6.3 (K), J14.1, R13.1, R14.1
unnamed: J1.2 (D-), J3.2
unnamed: J1.3 (D+), J3.3
unnamed: J2.3, J6.6, R5.1, U1.7 (B)
unnamed: J2.4, J6.5, R5.2, U1.6 (A)
unnamed: J4.1 (TD+), J8.6
unnamed: J4.2 (TD-), J8.5
unnamed: J4.3 (RD+), J8.1
unnamed: J4.6 (RD-), J8.2
unnamed: J4.9 (LED), J8.3
unnamed: J5.5, KF3.3
unnamed: J5.6, KF3.2
unnamed: J6.1, K1.5
unnamed: J6.2, U6.3 (IP-), U6.4 (IP-)
unnamed: J6.3, U5.4
unnamed: J6.4, R13.2
unnamed: J6.7, U4.2
unnamed: J6.8, U3.2
unnamed: J6.9, U2.2
unnamed: J6.12, KF2.6
unnamed: J10.3, J11.3, J15.5, J17.9, R10.1
unnamed: J10.4, J11.4, J15.6, J17.8, R11.1
unnamed: J9.1, J13.2
unnamed: J9.2, J13.3
unnamed: J13.4, R12.2
unnamed: J13.13, R4.1
unnamed: J13.15, R10.2, R11.2
unnamed: J14.3, U1.3 (DE), U1.4 (DI)
unnamed: J14.4, U1.1 (RO)
unnamed: J14.5, U1.2 (~RE)
unnamed: J5.4, J14.6
unnamed: J5.3, J14.7
unnamed: J14.8, U2.4
unnamed: J17.3, J22.2
unnamed: J17.4, J20.3, J27.2 (White)
unnamed: J17.5, J20.4, J27.1 (Yellow)
unnamed: J17.6, J21.8
unnamed: J17.7, J21.7
unnamed: J17.10, J21.5
unnamed: J17.11, J21.4
unnamed: J17.12, J25.10
unnamed: J17.13, J26.6
unnamed: J18.2, U3.4
unnamed: J18.3, U4.4
unnamed: J18.4, J19.3
unnamed: J18.5, J19.4
unnamed: J18.6, J26.7
unnamed: J18.7, J26.8
unnamed: K1.3, KF2.4
unnamed: KF2.5, U6.1 (IP+), U6.2 (IP+)
unnamed: KF3.4, R6.2
unnamed: Q1.1 (B), R12.1
unnamed: R1.2, U2.1
unnamed: R2.2, U3.1
unnamed: R3.2, U4.1
unnamed: R4.2, U5.1
unnamed: R8.2, U6.7 (VIOUT)

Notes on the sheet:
Dir-22
PWM-23
Steer 2
Switch 1
Steer 1
SCL
SDA
3.3V
GND
LED
WAS (5V)
RS485 B
RS485 A
Encoder
Str Switch
Wrk Switch
Str 1
IO Ref
TX1
RX1
TX2(F9 RX)
RX2(F9 TX)
Switch 2
12V
PWM-37
DIR-36
Str 2
12V
TX2
RX2
Spd Pulse
VUSB
D_N
D_P
3V3
Can L
Can H
CRX
CTX
26 (5V)

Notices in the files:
parts and their libraries:
Copyright 2021 Accelerated Designs. All rights reserved.
